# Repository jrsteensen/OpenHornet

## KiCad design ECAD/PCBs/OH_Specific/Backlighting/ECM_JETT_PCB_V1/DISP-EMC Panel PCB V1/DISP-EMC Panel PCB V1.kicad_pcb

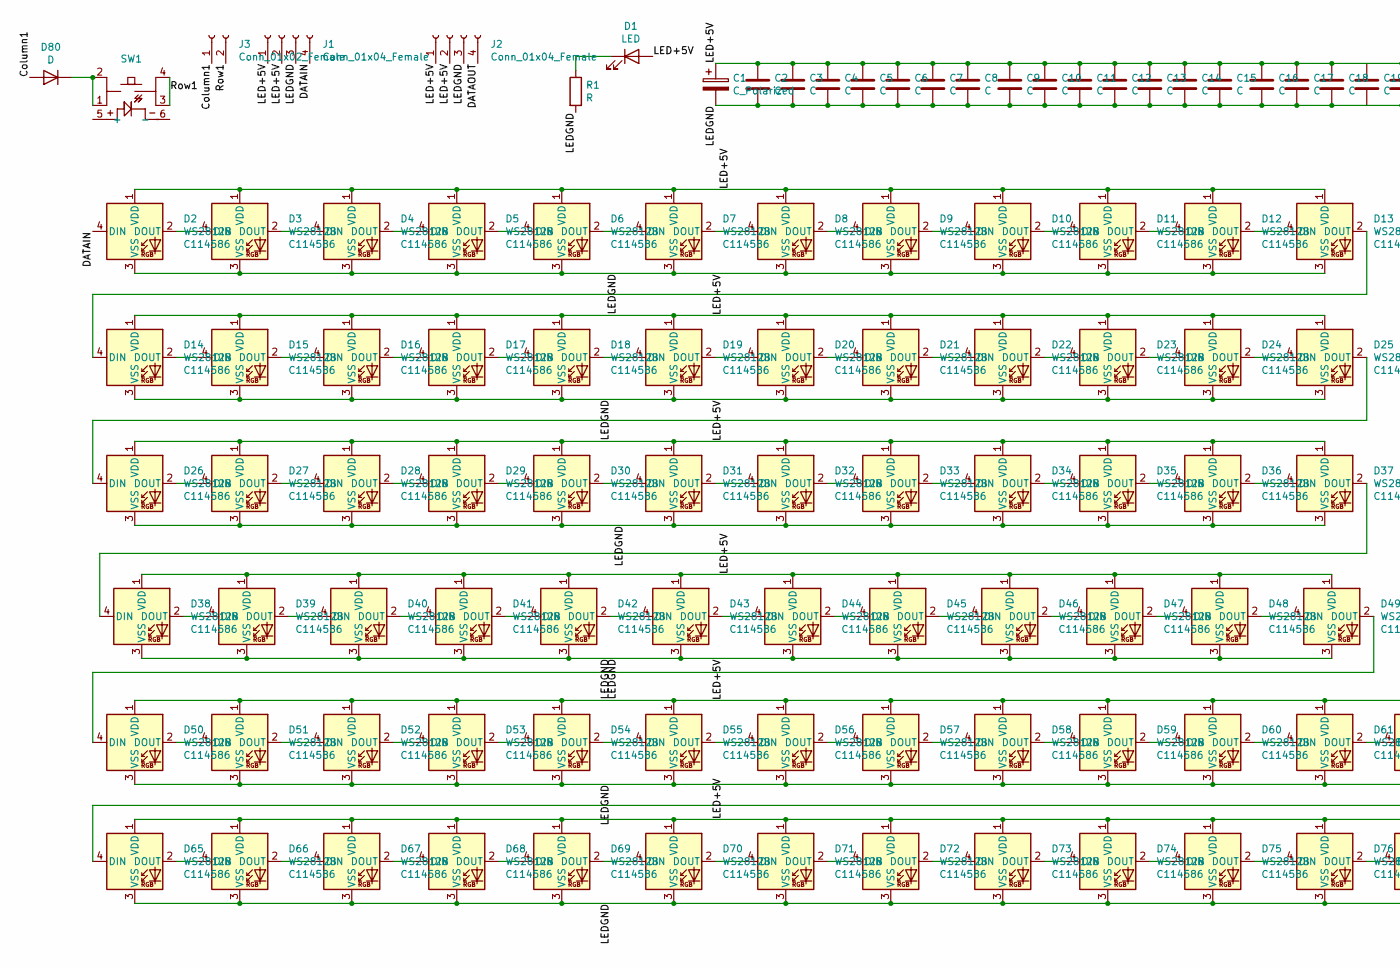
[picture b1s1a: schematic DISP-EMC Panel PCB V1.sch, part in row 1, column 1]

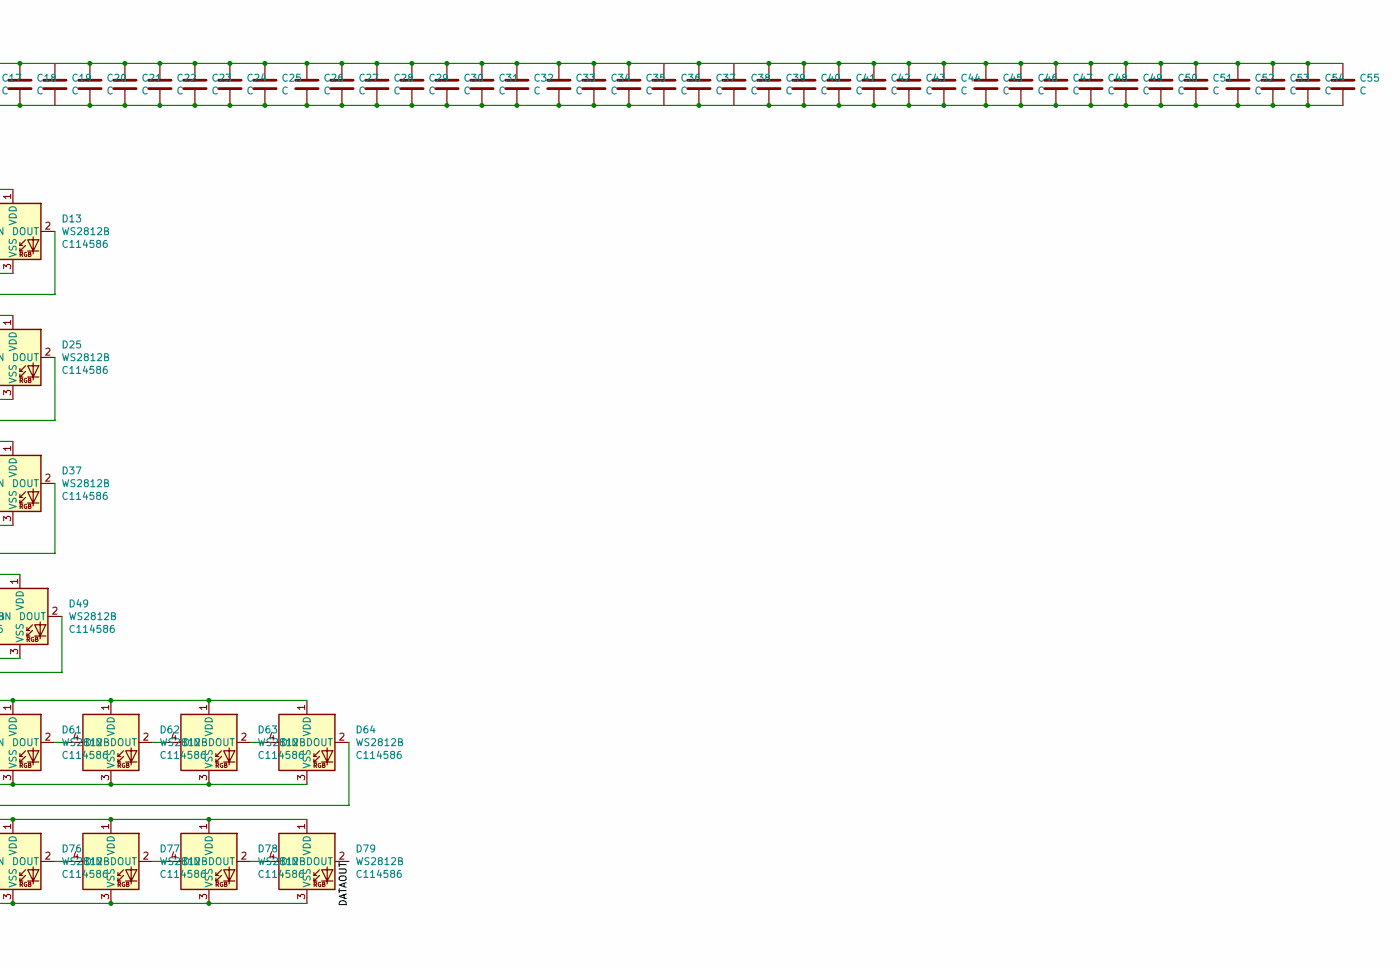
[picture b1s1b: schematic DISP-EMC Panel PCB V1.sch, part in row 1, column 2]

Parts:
C1: C_Polarized; CP_Elec_8x10
C2, C3, C4, C5, C6, C7, C8, C9, C10, C11, C12, C13, C14, C15, C16, C17, C18, C19, C20, C21, C22, C23, C24, C25, C26, C27, C28, C29, C30, C31, C32, C33, C34, C35, C36, C37, C38, C39, C40, C41, C42, C43, C44, C45, C46, C47, C48, C49, C50, C51, C52, C53, C54, C55: C; C_0603_1608Metric
D1: LED; LED_D3.0mm
D2, D3, D4, D5, D6, D7, D8, D9, D10, D11, D12, D13, D14, D15, D16, D17, D18, D19, D20, D21, D22, D23, D24, D25, D26, D27, D28, D29, D30, D31, D32, D33, D34, D35, D36, D37, D38, D39, D40, D41, D42, D43, D44, D45, D46, D47, D48, D49, D50, D51, D52, D53, D54, D55, D56, D57, D58, D59, D60, D61, D62, D63, D64, D65, D66, D67, D68, D69, D70, D71, D72, D73, D74, D75, D76, D77, D78, D79: WS2812B; LED_WS2812B_PLCC4_5.0x5.0mm_P3.2mm; LCSC Part Number C114586
D80: D; D_SOD-123
J1, J2: Conn_01x04_Female; Molex_Mini-Fit_Jr_5566-04A_2x02_P4.20mm_Vertical
J3: Conn_01x02_Female; Molex_KK-254_AE-6410-02A_1x02_P2.54mm_Vertical
R1: R; R_0603_1608Metric
SW1: PT_Tactile_Switch_Led; PT_Small_Tactile_Switch_With_LED

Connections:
/Column1: D80.2 (A), J3.1
/DATAIN: D2.4 (DIN), J1.4
/DATAOUT: D79.2 (DOUT), J2.4
/LED+5V: C1.1, C2.1, C3.1, C4.1, C5.1, C6.1, C7.1, C8.1, C9.1, C10.1, C11.1, C12.1, C13.1, C14.1, C15.1, C16.1, C17.1, C18.1, C19.1, C20.1, C21.1, C22.1, C23.1, C24.1, C25.1, C26.1, C27.1, C28.1, C29.1, C30.1, C31.1, C32.1, C33.1, C34.1, C35.1, C36.1, C37.1, C38.1, C39.1, C40.1, C41.1, C42.1, C43.1, C44.1, C45.1, C46.1, C47.1, C48.1, C49.1, C50.1, C51.1, C52.1, C53.1, C54.1, C55.1, D1.2 (A), D2.1 (VDD), D3.1 (VDD), D4.1 (VDD), D5.1 (VDD), D6.1 (VDD), D7.1 (VDD), D8.1 (VDD), D9.1 (VDD), D10.1 (VDD), D11.1 (VDD), D12.1 (VDD), D13.1 (VDD), D14.1 (VDD), D15.1 (VDD), D16.1 (VDD), D17.1 (VDD), D18.1 (VDD), D19.1 (VDD), D20.1 (VDD), D21.1 (VDD), D22.1 (VDD), D23.1 (VDD), D24.1 (VDD), D25.1 (VDD), D26.1 (VDD), D27.1 (VDD), D28.1 (VDD), D29.1 (VDD), D30.1 (VDD), D31.1 (VDD), D32.1 (VDD), D33.1 (VDD), D34.1 (VDD), D35.1 (VDD), D36.1 (VDD), D37.1 (VDD), D38.1 (VDD), D39.1 (VDD), D40.1 (VDD), D41.1 (VDD), D42.1 (VDD), D43.1 (VDD), D44.1 (VDD), D45.1 (VDD), D46.1 (VDD), D47.1 (VDD), D48.1 (VDD), D49.1 (VDD), D50.1 (VDD), D51.1 (VDD), D52.1 (VDD), D53.1 (VDD), D54.1 (VDD), D55.1 (VDD), D56.1 (VDD), D57.1 (VDD), D58.1 (VDD), D59.1 (VDD), D60.1 (VDD), D61.1 (VDD), D62.1 (VDD), D63.1 (VDD), D64.1 (VDD), D65.1 (VDD), D66.1 (VDD), D67.1 (VDD), D68.1 (VDD), D69.1 (VDD), D70.1 (VDD), D71.1 (VDD), D72.1 (VDD), D73.1 (VDD), D74.1 (VDD), D75.1 (VDD), D76.1 (VDD), D77.1 (VDD), D78.1 (VDD), D79.1 (VDD), J1.1, J1.2, J2.1, J2.2
/LEDGND: C1.2, C2.2, C3.2, C4.2, C5.2, C6.2, C7.2, C8.2, C9.2, C10.2, C11.2, C12.2, C13.2, C14.2, C15.2, C16.2, C17.2, C18.2, C19.2, C20.2, C21.2, C22.2, C23.2, C24.2, C25.2, C26.2, C27.2, C28.2, C29.2, C30.2, C31.2, C32.2, C33.2, C34.2, C35.2, C36.2, C37.2, C38.2, C39.2, C40.2, C41.2, C42.2, C43.2, C44.2, C45.2, C46.2, C47.2, C48.2, C49.2, C50.2, C51.2, C52.2, C53.2, C54.2, C55.2, D2.3 (VSS), D3.3 (VSS), D4.3 (VSS), D5.3 (VSS), D6.3 (VSS), D7.3 (VSS), D8.3 (VSS), D9.3 (VSS), D10.3 (VSS), D11.3 (VSS), D12.3 (VSS), D13.3 (VSS), D14.3 (VSS), D15.3 (VSS), D16.3 (VSS), D17.3 (VSS), D18.3 (VSS), D19.3 (VSS), D20.3 (VSS), D21.3 (VSS), D22.3 (VSS), D23.3 (VSS), D24.3 (VSS), D25.3 (VSS), D26.3 (VSS), D27.3 (VSS), D28.3 (VSS), D29.3 (VSS), D30.3 (VSS), D31.3 (VSS), D32.3 (VSS), D33.3 (VSS), D34.3 (VSS), D35.3 (VSS), D36.3 (VSS), D37.3 (VSS), D38.3 (VSS), D39.3 (VSS), D40.3 (VSS), D41.3 (VSS), D42.3 (VSS), D43.3 (VSS), D44.3 (VSS), D45.3 (VSS), D46.3 (VSS), D47.3 (VSS), D48.3 (VSS), D49.3 (VSS), D50.3 (VSS), D51.3 (VSS), D52.3 (VSS), D53.3 (VSS), D54.3 (VSS), D55.3 (VSS), D56.3 (VSS), D57.3 (VSS), D58.3 (VSS), D59.3 (VSS), D60.3 (VSS), D61.3 (VSS), D62.3 (VSS), D63.3 (VSS), D64.3 (VSS), D65.3 (VSS), D66.3 (VSS), D67.3 (VSS), D68.3 (VSS), D69.3 (VSS), D70.3 (VSS), D71.3 (VSS), D72.3 (VSS), D73.3 (VSS), D74.3 (VSS), D75.3 (VSS), D76.3 (VSS), D77.3 (VSS), D78.3 (VSS), D79.3 (VSS), J1.3, J2.3, R1.2
/Row1: J3.2, SW1.3, SW1.4
unnamed: D1.1 (K), R1.1
unnamed: D2.2 (DOUT), D3.4 (DIN)
unnamed: D3.2 (DOUT), D4.4 (DIN)
unnamed: D4.2 (DOUT), D5.4 (DIN)
unnamed: D5.2 (DOUT), D6.4 (DIN)
unnamed: D6.2 (DOUT), D7.4 (DIN)
unnamed: D7.2 (DOUT), D8.4 (DIN)
unnamed: D8.2 (DOUT), D9.4 (DIN)
unnamed: D10.2 (DOUT), D11.4 (DIN)
unnamed: D9.2 (DOUT), D10.4 (DIN)
unnamed: D11.2 (DOUT), D12.4 (DIN)
unnamed: D12.2 (DOUT), D13.4 (DIN)
unnamed: D13.2 (DOUT), D14.4 (DIN)
unnamed: D14.2 (DOUT), D15.4 (DIN)
unnamed: D15.2 (DOUT), D16.4 (DIN)
unnamed: D16.2 (DOUT), D17.4 (DIN)
unnamed: D17.2 (DOUT), D18.4 (DIN)
unnamed: D18.2 (DOUT), D19.4 (DIN)
unnamed: D19.2 (DOUT), D20.4 (DIN)
unnamed: D20.2 (DOUT), D21.4 (DIN)
unnamed: D21.2 (DOUT), D22.4 (DIN)
unnamed: D22.2 (DOUT), D23.4 (DIN)
unnamed: D23.2 (DOUT), D24.4 (DIN)
unnamed: D24.2 (DOUT), D25.4 (DIN)
unnamed: D25.2 (DOUT), D26.4 (DIN)
unnamed: D26.2 (DOUT), D27.4 (DIN)
unnamed: D27.2 (DOUT), D28.4 (DIN)
unnamed: D28.2 (DOUT), D29.4 (DIN)
unnamed: D29.2 (DOUT), D30.4 (DIN)
unnamed: D30.2 (DOUT), D31.4 (DIN)
unnamed: D31.2 (DOUT), D32.4 (DIN)
unnamed: D32.2 (DOUT), D33.4 (DIN)
unnamed: D33.2 (DOUT), D34.4 (DIN)
unnamed: D34.2 (DOUT), D35.4 (DIN)
unnamed: D35.2 (DOUT), D36.4 (DIN)
unnamed: D36.2 (DOUT), D37.4 (DIN)
unnamed: D37.2 (DOUT), D38.4 (DIN)
unnamed: D38.2 (DOUT), D39.4 (DIN)
unnamed: D39.2 (DOUT), D40.4 (DIN)
unnamed: D40.2 (DOUT), D41.4 (DIN)
unnamed: D41.2 (DOUT), D42.4 (DIN)
unnamed: D42.2 (DOUT), D43.4 (DIN)
unnamed: D43.2 (DOUT), D44.4 (DIN)
unnamed: D44.2 (DOUT), D45.4 (DIN)
unnamed: D45.2 (DOUT), D46.4 (DIN)
unnamed: D46.2 (DOUT), D47.4 (DIN)
unnamed: D47.2 (DOUT), D48.4 (DIN)
unnamed: D48.2 (DOUT), D49.4 (DIN)
unnamed: D49.2 (DOUT), D50.4 (DIN)
unnamed: D50.2 (DOUT), D51.4 (DIN)
unnamed: D51.2 (DOUT), D52.4 (DIN)
unnamed: D52.2 (DOUT), D53.4 (DIN)
unnamed: D53.2 (DOUT), D54.4 (DIN)
unnamed: D54.2 (DOUT), D55.4 (DIN)
unnamed: D55.2 (DOUT), D56.4 (DIN)
unnamed: D56.2 (DOUT), D57.4 (DIN)
unnamed: D57.2 (DOUT), D58.4 (DIN)
unnamed: D58.2 (DOUT), D59.4 (DIN)
unnamed: D59.2 (DOUT), D60.4 (DIN)
unnamed: D60.2 (DOUT), D61.4 (DIN)
unnamed: D61.2 (DOUT), D62.4 (DIN)
unnamed: D62.2 (DOUT), D63.4 (DIN)
unnamed: D63.2 (DOUT), D64.4 (DIN)
unnamed: D64.2 (DOUT), D65.4 (DIN)
unnamed: D65.2 (DOUT), D66.4 (DIN)
unnamed: D66.2 (DOUT), D67.4 (DIN)
unnamed: D67.2 (DOUT), D68.4 (DIN)
unnamed: D68.2 (DOUT), D69.4 (DIN)
unnamed: D69.2 (DOUT), D70.4 (DIN)
unnamed: D70.2 (DOUT), D71.4 (DIN)
unnamed: D71.2 (DOUT), D72.4 (DIN)
unnamed: D72.2 (DOUT), D73.4 (DIN)
unnamed: D73.2 (DOUT), D74.4 (DIN)
unnamed: D74.2 (DOUT), D75.4 (DIN)
unnamed: D75.2 (DOUT), D76.4 (DIN)
unnamed: D76.2 (DOUT), D77.4 (DIN)
unnamed: D77.2 (DOUT), D78.4 (DIN)
unnamed: D78.2 (DOUT), D79.4 (DIN)
unnamed: D80.1 (K), SW1.1, SW1.2

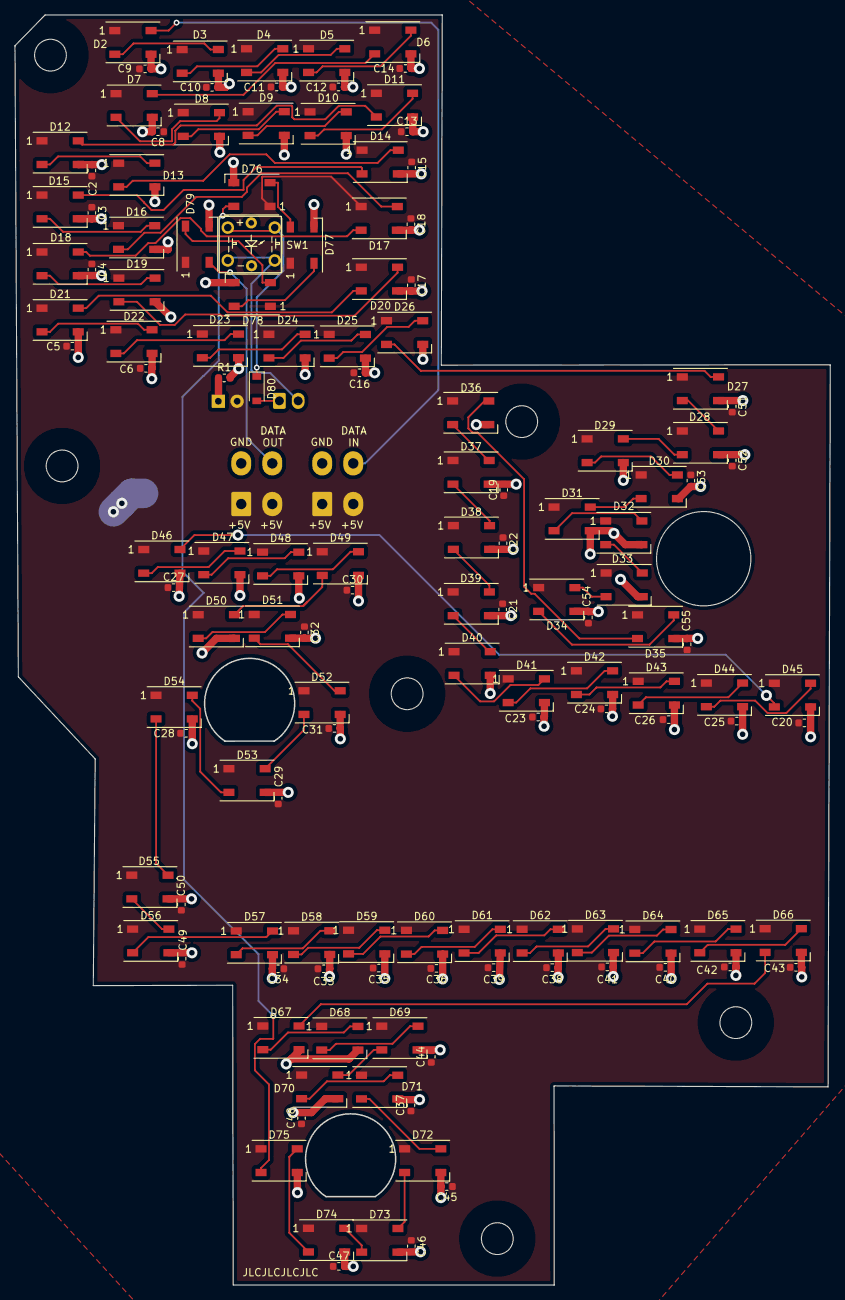
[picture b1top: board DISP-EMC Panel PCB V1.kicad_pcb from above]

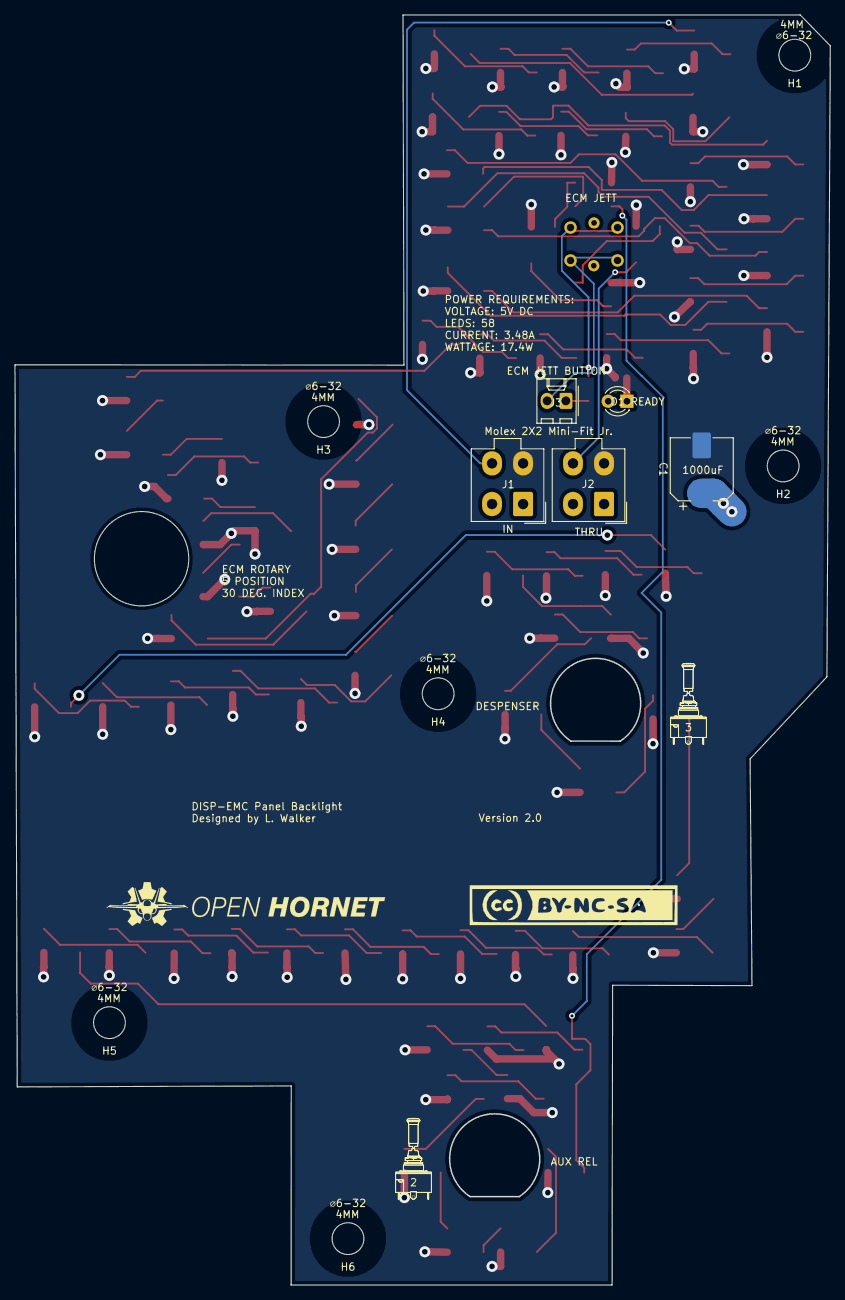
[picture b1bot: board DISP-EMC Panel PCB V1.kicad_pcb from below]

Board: 2 copper layers, 110.3 x 171.8 mm, 146 parts (5 on the bottom side), 85 nets.

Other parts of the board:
1, 3, 3#2, 4, 5, 6: OH_Panel_Fastner_Keepout; OH_Panel_6-32_PHS
G1: S3AL Toggle; S3AL_Toggle_Silkscreen

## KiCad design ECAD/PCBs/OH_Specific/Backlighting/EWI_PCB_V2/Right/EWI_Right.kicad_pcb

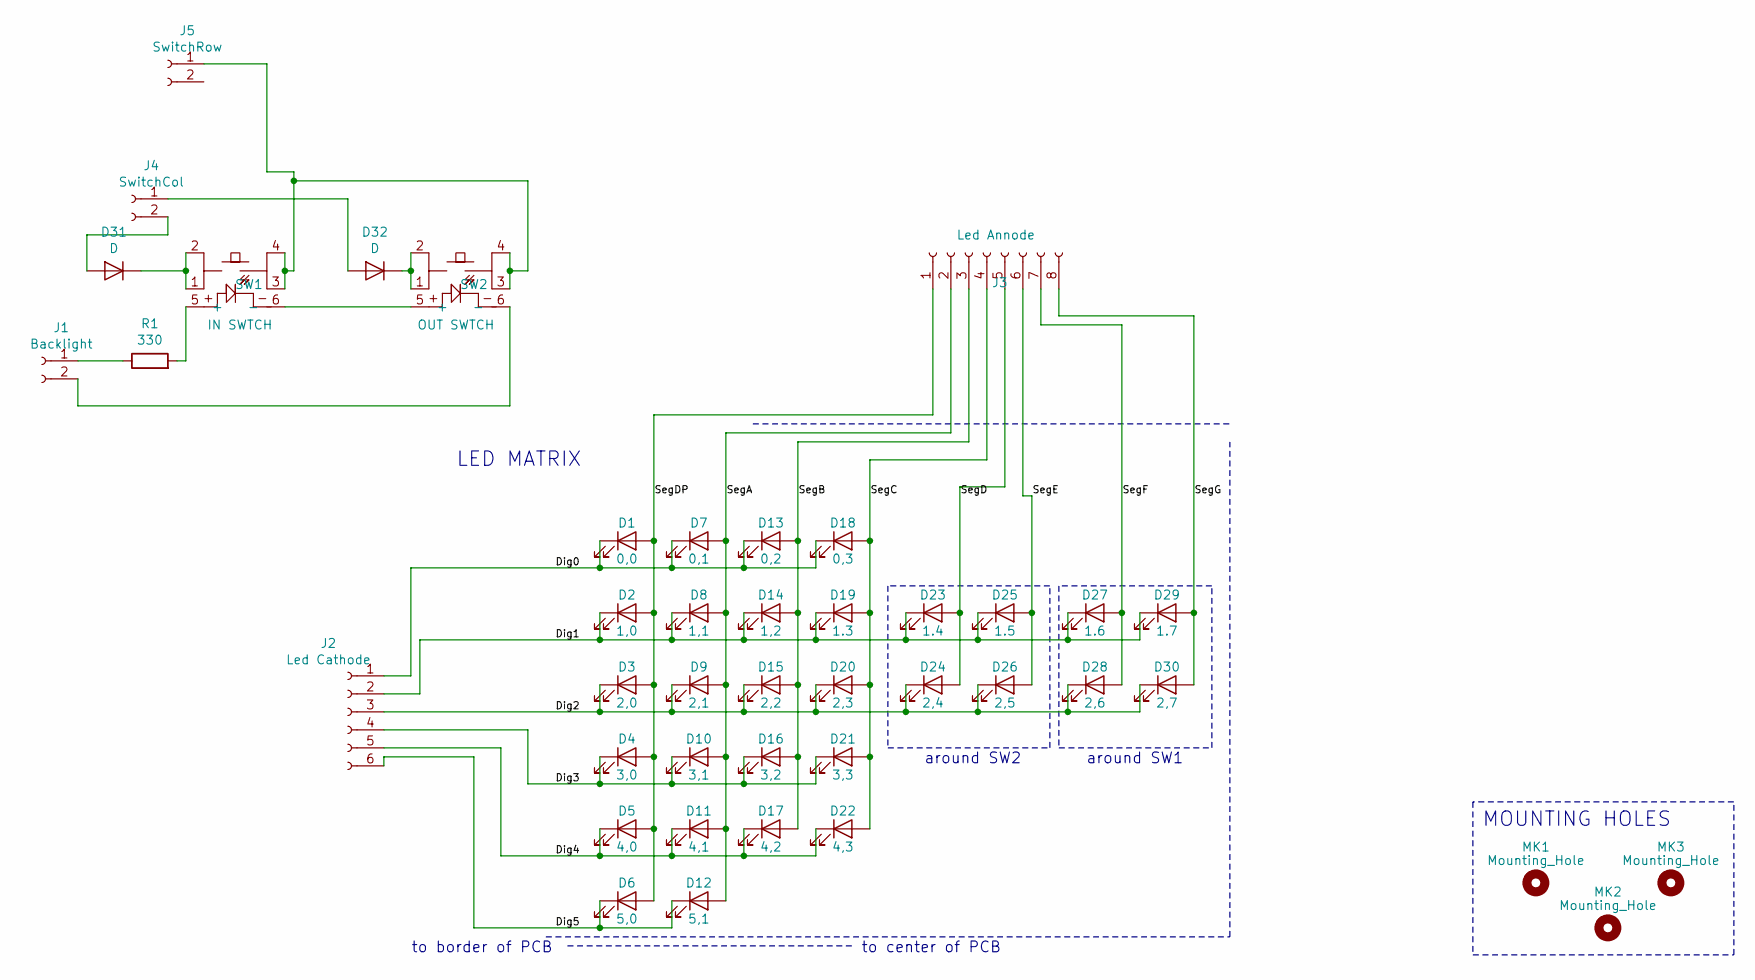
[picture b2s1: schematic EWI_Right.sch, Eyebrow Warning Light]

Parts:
D1: 0,0; LED_D3.0mm_FlatTop
D2: 1,0; LED_D3.0mm_FlatTop
D3: 2,0; LED_D3.0mm_FlatTop
D4: 3,0; LED_D3.0mm_FlatTop
D5: 4,0; LED_D3.0mm_FlatTop
D6: 5,0; LED_D3.0mm_FlatTop
D7: 0,1; LED_D3.0mm_FlatTop
D8: 1,1; LED_D3.0mm_FlatTop
D9: 2,1; LED_D3.0mm_FlatTop
D10: 3,1; LED_D3.0mm_FlatTop
D11: 4,1; LED_D3.0mm_FlatTop
D12: 5,1; LED_D3.0mm_FlatTop
D13: 0,2; LED_D3.0mm_FlatTop
D14: 1,2; LED_D3.0mm_FlatTop
D15: 2,2; LED_D3.0mm_FlatTop
D16: 3,2; LED_D3.0mm_FlatTop
D17: 4,2; LED_D3.0mm_FlatTop
D18: 0,3; LED_D3.0mm_FlatTop
D19: 1.3; LED_D3.0mm_FlatTop
D20: 2,3; LED_D3.0mm_FlatTop
D21: 3,3; LED_D3.0mm_FlatTop
D22: 4,3; LED_D3.0mm_FlatTop
D23: 1.4; LED_D3.0mm_FlatTop
D24: 2,4; LED_D3.0mm_FlatTop
D25: 1.5; LED_D3.0mm_FlatTop
D26: 2,5; LED_D3.0mm_FlatTop
D27: 1.6; LED_D3.0mm_FlatTop
D28: 2,6; LED_D3.0mm_FlatTop
D29: 1.7; LED_D3.0mm_FlatTop
D30: 2,7; LED_D3.0mm_FlatTop
D31, D32: D; D_Signal_P7.62mm_Horizontal
J1: Backlight; Molex_1x02_P2.54mm_Vertical
J2: Led Cathode; Molex_1x06_P2.54mm_Vertical
J3: Led Annode; Molex_1x08_P2.54mm_Vertical
J4: SwitchCol; Molex_1x02_P2.54mm_Vertical
J5: SwitchRow; Molex_1x02_P2.54mm_Vertical
MK1, MK2, MK3: Mounting_Hole; MountingHole_2.5mm
R1: 330; R_Axial_DIN0207_L6.3mm_D2.5mm_P7.62mm_Horizontal
SW1: IN SWTCH; PT_Small_Tactile_Switch_With_LED
SW2: OUT SWTCH; PT_Small_Tactile_Switch_With_LED

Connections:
/Dig0: D1.1 (K), D7.1 (K), D13.1 (K), D18.1 (K), J2.1
/Dig1: D2.1 (K), D8.1 (K), D14.1 (K), D19.1 (K), D23.1 (K), D25.1 (K), D27.1 (K), D29.1 (K), J2.2
/Dig2: D3.1 (K), D9.1 (K), D15.1 (K), D20.1 (K), D24.1 (K), D26.1 (K), D28.1 (K), D30.1 (K), J2.3
/Dig3: D4.1 (K), D10.1 (K), D16.1 (K), D21.1 (K), J2.4
/Dig4: D5.1 (K), D11.1 (K), D17.1 (K), D22.1 (K), J2.5
/Dig5: D6.1 (K), D12.1 (K), J2.6
/SegA: D7.2 (A), D8.2 (A), D9.2 (A), D10.2 (A), D11.2 (A), D12.2 (A), J3.2
/SegB: D13.2 (A), D14.2 (A), D15.2 (A), D16.2 (A), D17.2 (A), J3.3
/SegC: D18.2 (A), D19.2 (A), D20.2 (A), D21.2 (A), D22.2 (A), J3.4
/SegD: D23.2 (A), D24.2 (A), J3.5
/SegDP: D1.2 (A), D2.2 (A), D3.2 (A), D4.2 (A), D5.2 (A), D6.2 (A), J3.1
/SegE: D25.2 (A), D26.2 (A), J3.6
/SegF: D27.2 (A), D28.2 (A), J3.7
/SegG: D29.2 (A), D30.2 (A), J3.8
unnamed: D31.1 (K), SW1.1, SW1.2
unnamed: D31.2 (A), J4.2
unnamed: D32.1 (K), SW2.1, SW2.2
unnamed: D32.2 (A), J4.1
unnamed: J1.1, R1.1
unnamed: J1.2, SW2.6 (-)
unnamed: J5.1, SW1.3, SW1.4, SW2.3, SW2.4
unnamed: R1.2, SW1.5 (+)
unnamed: SW1.6 (-), SW2.5 (+)

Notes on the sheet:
MOUNTING HOLES
LED MATRIX
around SW1
around SW2
to center of PCB
to border of PCB

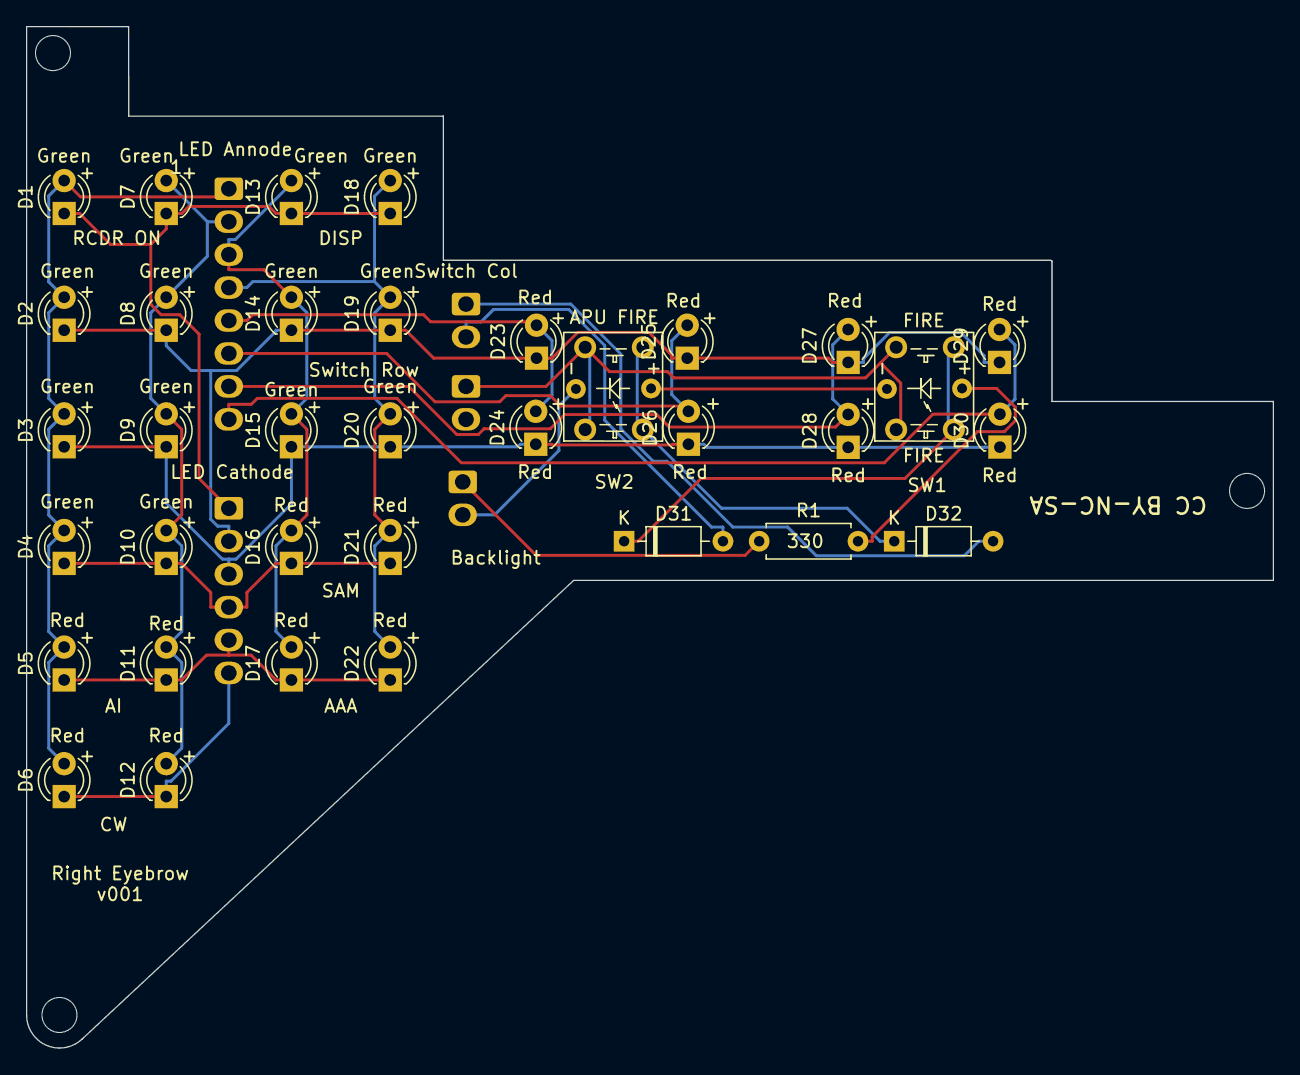
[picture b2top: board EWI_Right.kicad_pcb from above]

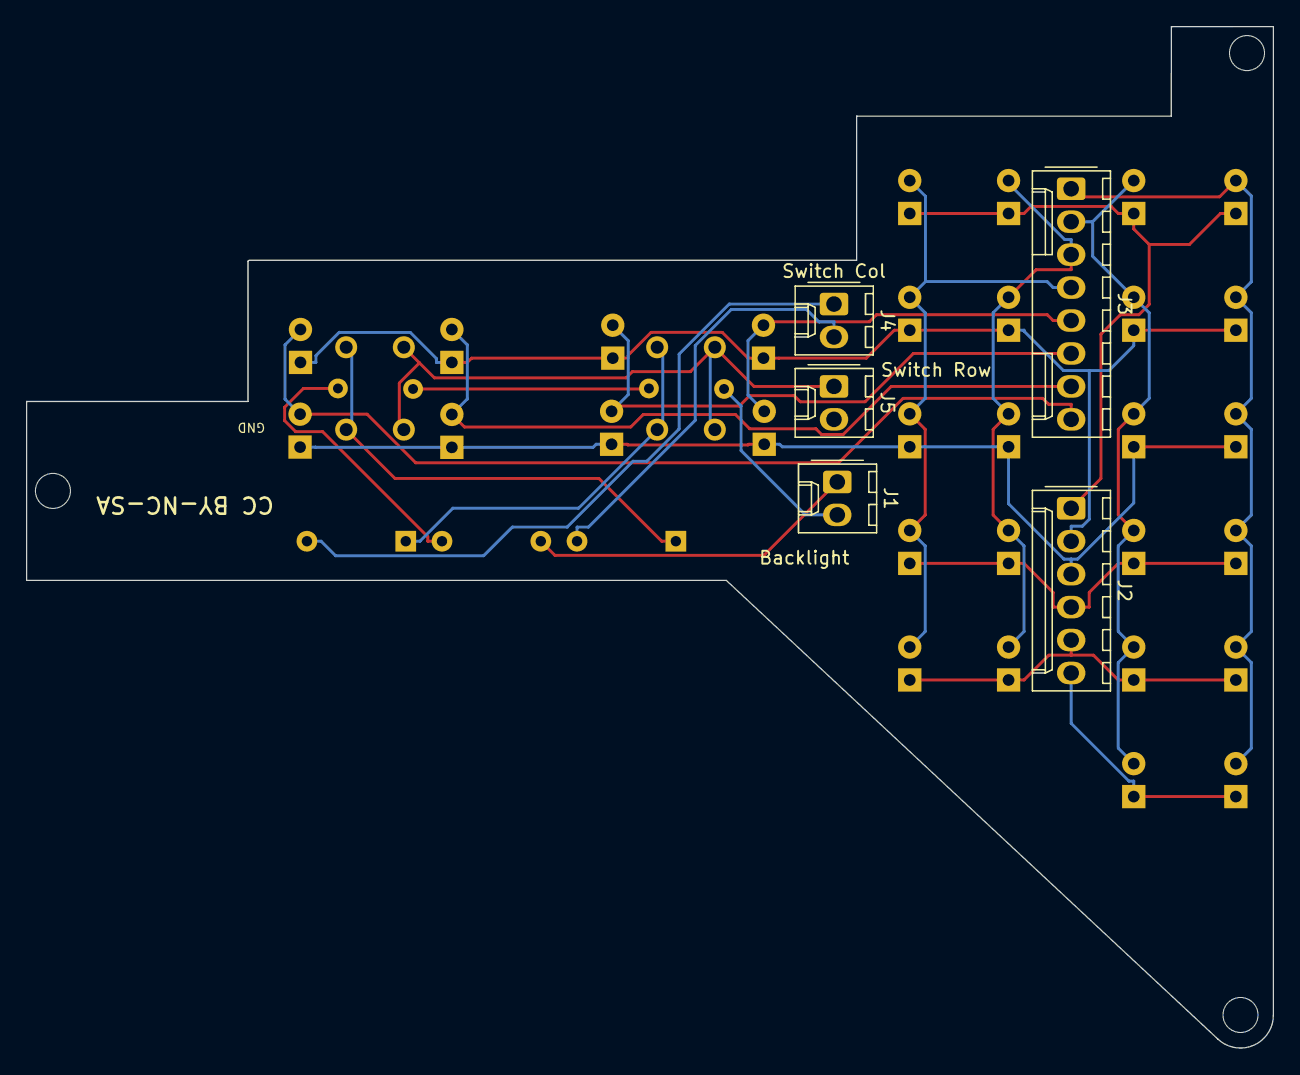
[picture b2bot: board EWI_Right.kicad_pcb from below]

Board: 2 copper layers, 96.1 x 78.8 mm, 43 parts (8 on the bottom side), 23 nets.

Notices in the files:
ECAD/PCBs/OH_Specific/Backlighting/EWI_PCB_V2/Right/EWI_Right.kicad_pcb:
CC BY-NC-SA
